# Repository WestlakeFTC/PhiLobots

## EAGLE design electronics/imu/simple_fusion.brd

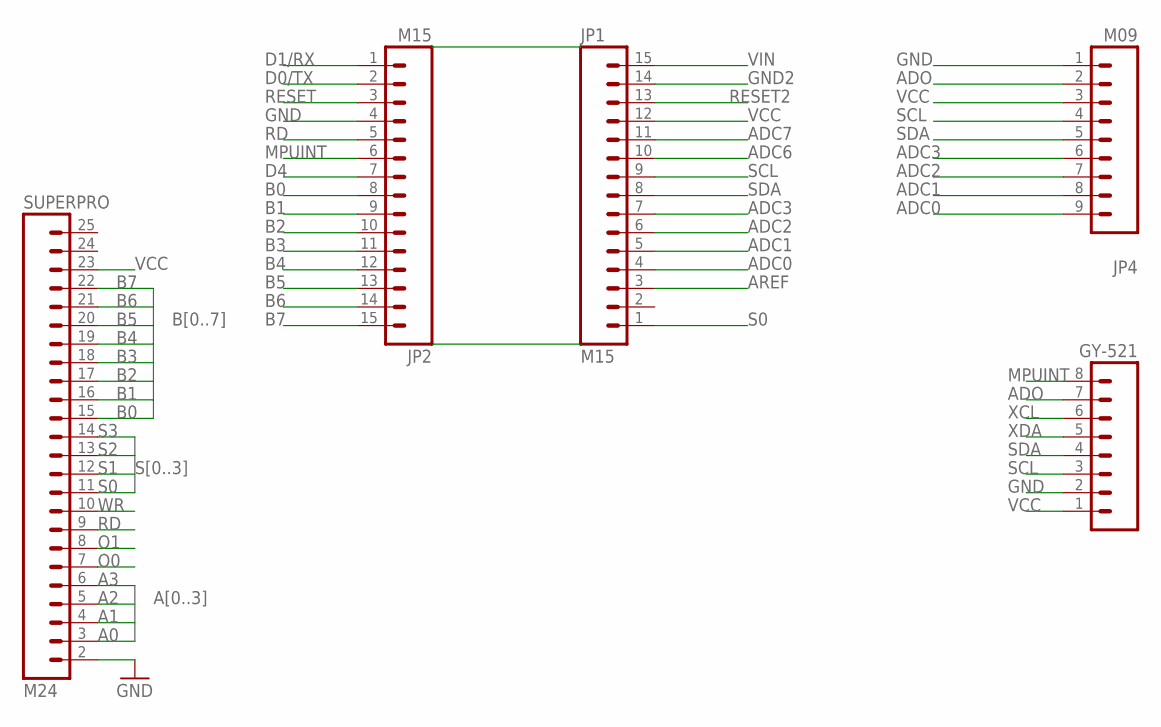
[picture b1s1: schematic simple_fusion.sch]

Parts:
GY-521: M081X08; 1X08
JP1, JP2: M15; 1X15
JP4: M09; 1X09
SUPERPRO: M24; 1X24

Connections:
A0: SUPERPRO.3
A1: SUPERPRO.4
A2: SUPERPRO.5
A3: SUPERPRO.6
ADC0: JP1.4, JP4.9
ADC1: JP1.5, JP4.8
ADC2: JP1.6, JP4.7
ADC3: JP1.7, JP4.6
ADC6: JP1.10
ADC7: JP1.11
ADO: GY-521.7, JP4.2
AREF: JP1.3
B0: JP2.8, SUPERPRO.15
B1: JP2.9, SUPERPRO.16
B2: JP2.10, SUPERPRO.17
B3: JP2.11, SUPERPRO.18
B4: JP2.12, SUPERPRO.19
B5: JP2.13, SUPERPRO.20
B6: JP2.14, SUPERPRO.21
B7: JP2.15, SUPERPRO.22
D0/TX: JP2.2
D1/RX: JP2.1
D4: JP2.7
GND: GY-521.2, JP2.4, JP4.1, SUPERPRO.2
GND2: JP1.14
MPUINT: GY-521.8, JP2.6
O0: SUPERPRO.7
O1: SUPERPRO.8
RD: JP2.5, SUPERPRO.9
RESET: JP2.3
RESET2: JP1.13
S0: JP1.1, SUPERPRO.11
S1: SUPERPRO.12
S2: SUPERPRO.13
S3: SUPERPRO.14
SCL: GY-521.3, JP1.9, JP4.4
SDA: GY-521.4, JP1.8, JP4.5
VCC: GY-521.1, JP1.12, JP4.3, SUPERPRO.23
VIN: JP1.15
WR: SUPERPRO.10
XCL: GY-521.6
XDA: GY-521.5

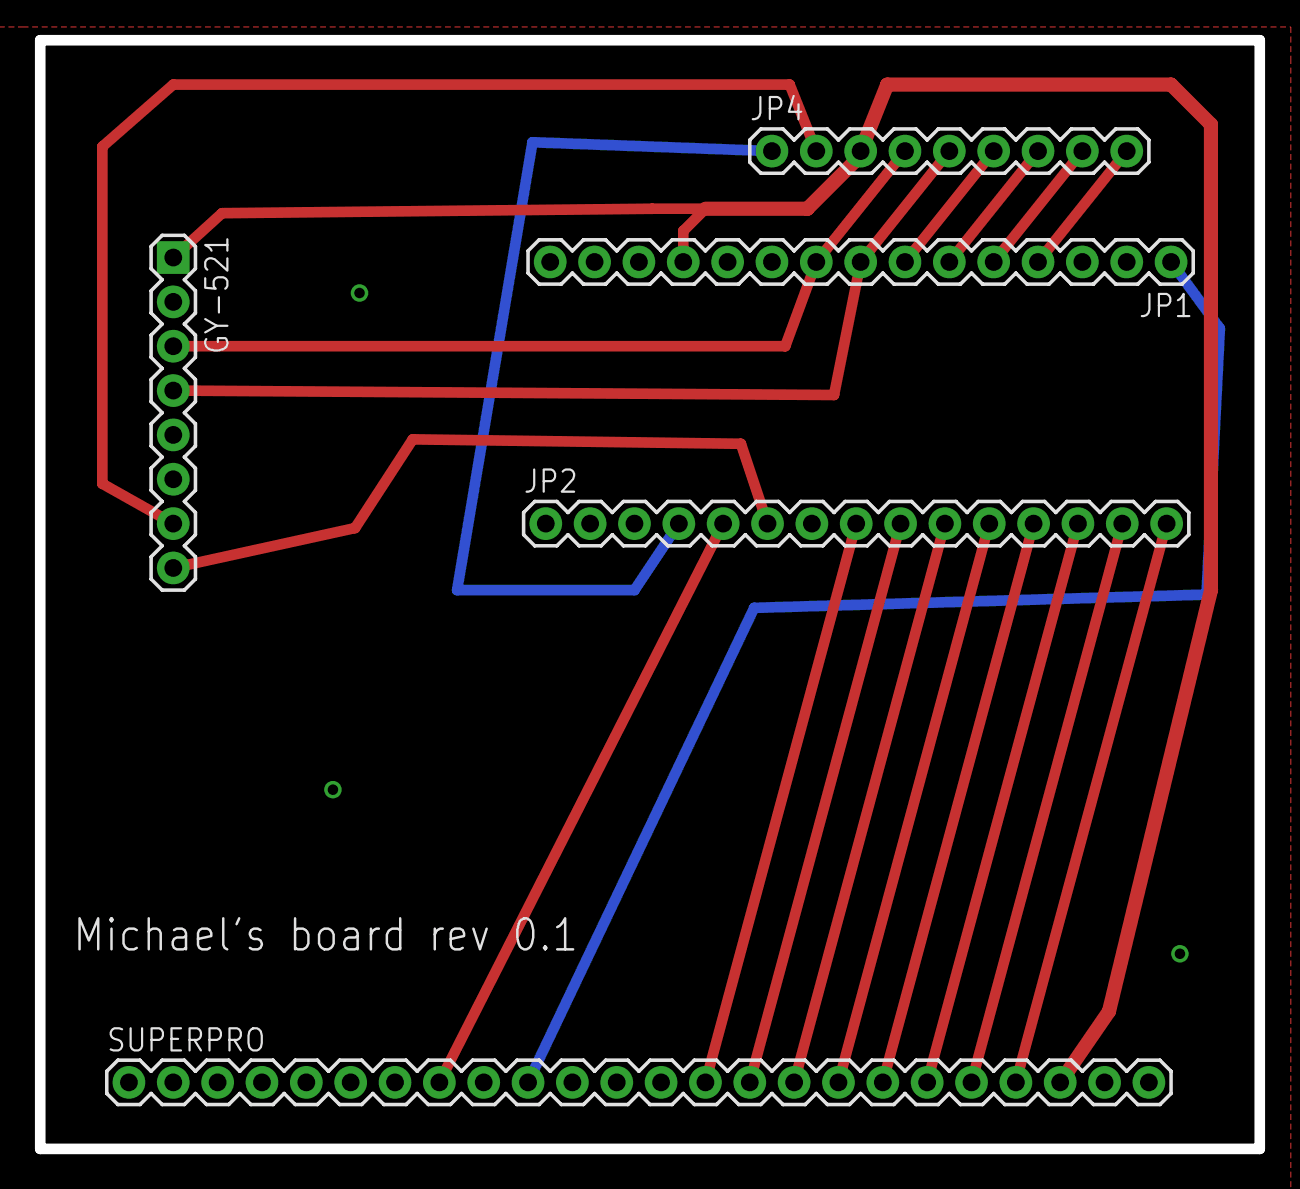
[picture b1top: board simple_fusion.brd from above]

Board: 2 copper layers, 69.8 x 63.5 mm, 5 parts (0 on the bottom side), 20 nets.

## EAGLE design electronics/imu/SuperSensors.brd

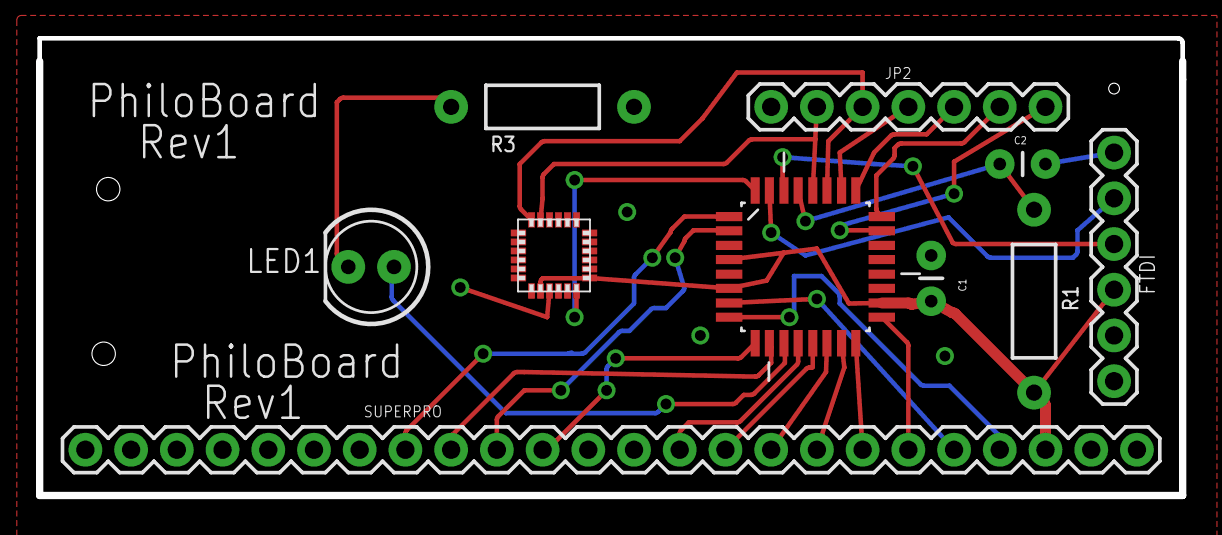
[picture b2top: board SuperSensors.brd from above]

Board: 2 copper layers, 63.5 x 25.3 mm, 10 parts (0 on the bottom side), 27 nets.

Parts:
C1, C2: 0.1uF; CAP-PTH-SMALL
FTDI: FTDI; 1X06
JP2: 1X07
LED1: 0.25W; LED5MM
R1, R3: 21K; AXIAL-0.4
SUPERPRO: M24; 1X24
U1: QFP80P900X900X120-32N
U$1: MPU-6050; QFN.24.4X4

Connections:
ADC0: JP2.7, U1.23
ADC1: JP2.6, U1.24
ADC2: JP2.5, U1.25
ADC3: JP2.4, U1.26
B0: SUPERPRO.15, U1.12
B1: SUPERPRO.16, U1.13
B2: SUPERPRO.17, U1.14
B3: SUPERPRO.18, U1.15
B4: SUPERPRO.19, U1.16
B5: SUPERPRO.20, U1.17
B6: SUPERPRO.21, U1.7
B7: SUPERPRO.22, U1.8
DTR: C2.1, FTDI.1
GND: C1.1, FTDI.6, JP2.1, R3.P$1, SUPERPRO.2, U1.3, U1.5, U1.21, U$1.9, U$1.18
MPUINT: U1.32, U$1.12
unnamed: LED1.A, U1.11
unnamed: LED1.K, R3.P$2
RD: SUPERPRO.9, U1.1
RESET: C2.2, R1.P$2, U1.29
RX: FTDI.3, U1.30
S0: SUPERPRO.11, U1.2
S1: SUPERPRO.12, U1.9
SCL: JP2.2, U1.28, U$1.23
SDA: JP2.3, U1.27, U$1.24
TX: FTDI.2, U1.31
VCC: C1.2, FTDI.4, R1.P$1, SUPERPRO.23, U1.4, U1.6, U1.18, U$1.8, U$1.13
WR: SUPERPRO.10, U1.10

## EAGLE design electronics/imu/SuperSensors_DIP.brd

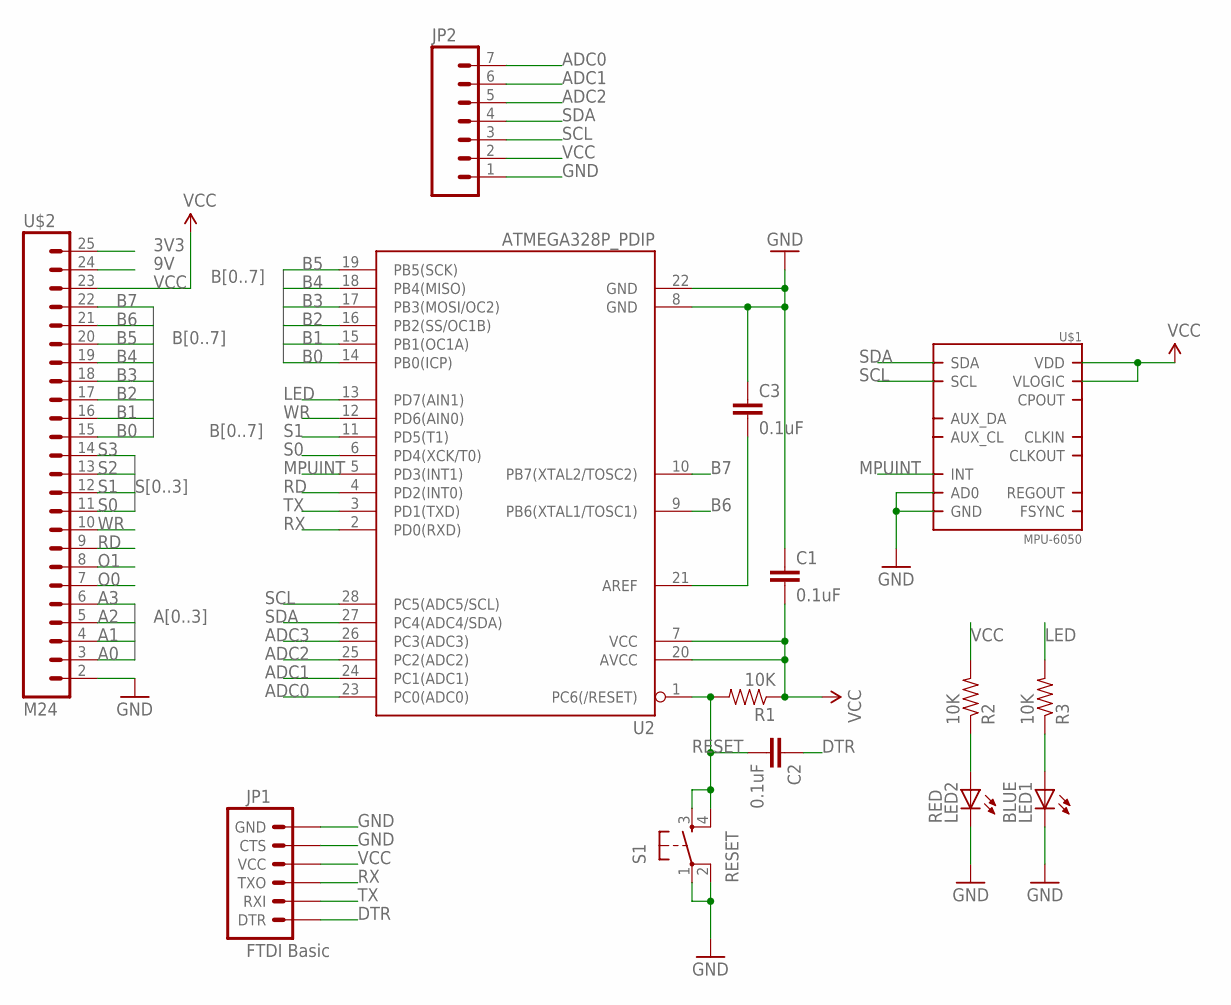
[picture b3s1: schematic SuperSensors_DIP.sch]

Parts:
C1, C2, C3: 0.1uF; CAP-PTH-SMALL
JP1: FTDI Basic; 1X06
JP2: M07; 1X07
LED1: BLUE; LED5MM
LED2: RED; LED5MM
R1, R2, R3: 10K; AXIAL-0.4
S1: RESET; TACTILE_SWITCH_SMD
U2: ATMEGA328P_PDIP; DIL28-3
U$1: MPU-6050; QFN.24.4X4
U$2: M24; 1X24

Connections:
3V3: U$2.25
9V: U$2.24
A0: U$2.3
A1: U$2.4
A2: U$2.5
A3: U$2.6
ADC0: JP2.7, U2.23 (PC0(ADC0))
ADC1: JP2.6, U2.24 (PC1(ADC1))
ADC2: JP2.5, U2.25 (PC2(ADC2))
ADC3: U2.26 (PC3(ADC3))
B0: U2.14 (PB0(ICP)), U$2.15
B1: U2.15 (PB1(OC1A)), U$2.16
B2: U2.16 (PB2(SS/OC1B)), U$2.17
B3: U2.17 (PB3(MOSI/OC2)), U$2.18
B4: U2.18 (PB4(MISO)), U$2.19
B5: U2.19 (PB5(SCK)), U$2.20
B6: U2.9 (PB6(XTAL1/TOSC1)), U$2.21
B7: U2.10 (PB7(XTAL2/TOSC2)), U$2.22
DTR: C2.1, JP1.1 (DTR)
GND: C1.1, C3.1, JP1.5 (CTS), JP1.6 (GND), JP2.1, LED1.K (C), LED2.K (C), S1.1, S1.2, U2.8 (GND), U2.22 (GND), U$1.9 (AD0), U$1.18 (GND), U$2.2
LED: R3.P$2 (2), U2.13 (PD7(AIN1))
MPUINT: U2.5 (PD3(INT1)), U$1.12 (INT)
unnamed: LED2.A, R2.P$1 (1)
unnamed: C3.2, U2.21 (AREF)
unnamed: LED1.A, R3.P$1 (1)
O0: U$2.7
O1: U$2.8
RD: U2.4 (PD2(INT0)), U$2.9
RESET: C2.2, R1.P$2 (2), S1.3, S1.4, U2.1 (PC6(/RESET))
RX: JP1.3 (TXO), U2.2 (PD0(RXD))
S0: U2.6 (PD4(XCK/T0)), U$2.11
S1: U2.11 (PD5(T1)), U$2.12
S2: U$2.13
S3: U$2.14
SCL: JP2.3, U2.28 (PC5(ADC5/SCL)), U$1.23 (SCL)
SDA: JP2.4, U2.27 (PC4(ADC4/SDA)), U$1.24 (SDA)
TX: JP1.2 (RXI), U2.3 (PD1(TXD))
VCC: C1.2, JP1.4 (VCC), JP2.2, R1.P$1 (1), R2.P$2 (2), U2.7 (VCC), U2.20 (AVCC), U$1.8 (VLOGIC), U$1.13 (VDD), U$2.23
WR: U2.12 (PD6(AIN0)), U$2.10

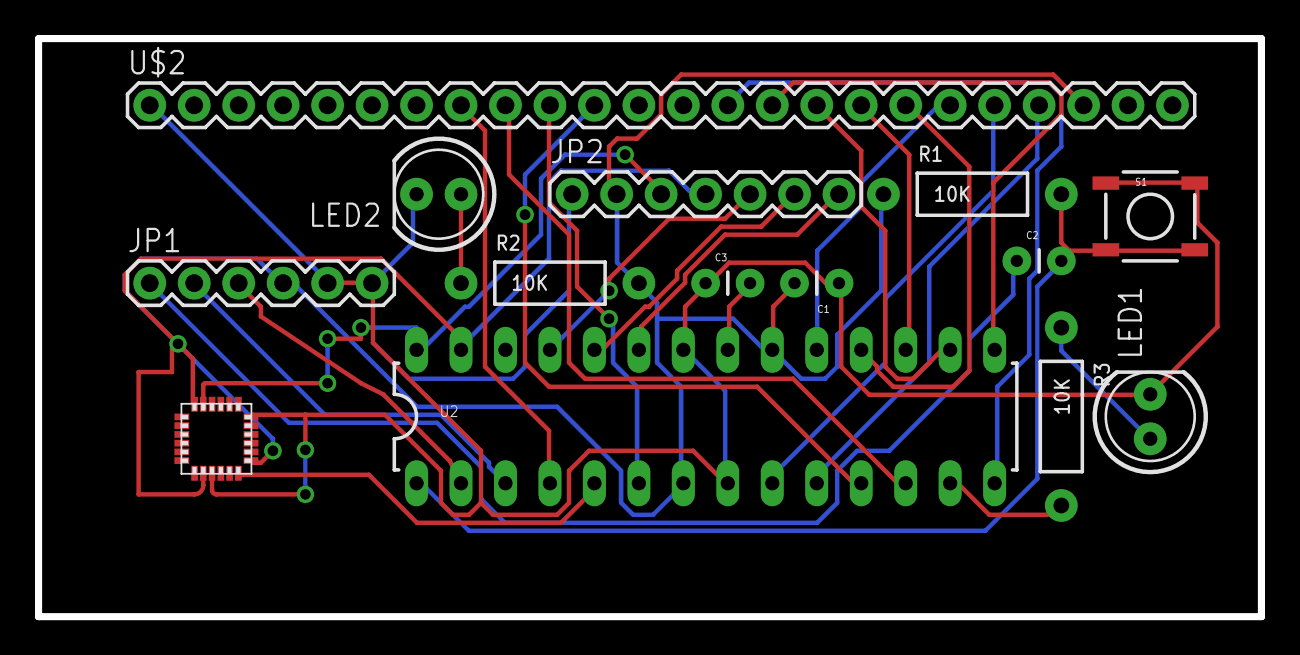
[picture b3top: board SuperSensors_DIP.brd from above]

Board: 2 copper layers, 69.8 x 33.0 mm, 14 parts (0 on the bottom side), 28 nets.

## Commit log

2014-10-23 add current prototype
2014-10-31 more prototyping
    added encoder, sonar sensor code
    clean up too
    added draft autonomous
2014-11-05 Autonomous TroubleShoot
    fixed turn function
2014-11-19 added predicted and observed offset
2014-11-24 teleop
    updated systems
2014-11-26 teleop for insertion
    first version
2014-11-28 Button woes resolved
    figured out unresponsive button problem with debouncing
2014-11-28 faucet direction
    aiming system
2014-11-29 Using objects in robotC? Mind Explosion
    Definition of object like structure to debounce every button
2014-11-29 name consistency + glass jar resolution
2014-11-29 control
2014-11-29 Autonomous + glass jar resolution
2014-11-29 same code except for one 1
2014-12-02 Lift control
    add lift control, also clean up a little
2014-12-02 adjust lift control
    make it less sensitive so more accurate control
2014-12-03 parkinglot autonomous
    fine tuned the movements
2014-12-03 grabber control
    add grabber control with d-pad (top hat) buttons
2014-12-05 Ramp+teleop
2014-12-05 clean up ultrasound
    assume position 3 when in doubt
2014-12-05 comments
    add/adjust comments
2014-12-06 reconfigure
    reconfigure to match current eclectronics
    adjust trailer
    add ramp to goal autonomous
2014-12-06 practice
    adjust based on practice
2014-12-06 ramp
    match ramp numbers to parking lot testing
2014-12-06 adjust
    ramp2goal
2014-12-25 shinning new grabber
    and some attempt on ramp autonomous strategy
2015-01-01 grabber work for most cases
    still need work on cases when goal is at horizontal
2015-01-01 working grabber backup
    The grabber work for pretty much everything but imma make it better
2015-01-01 Working grabber back up is the best option
2015-01-08 initial schematics for sensor board
2015-01-09 adjust wiggle to goal
    slowed down some speeds and added slower turn to wiggle
2015-01-11 lots of changes
    Multiplexer is here too
2015-01-11 flapper installed
    initial positions for flappers for teleop
2015-01-16 gear ratio
2015-01-17 board layout
2015-01-17 fixing some short circuits
2015-01-23 tune for new driver train
2015-01-23 more tune
2015-01-24 add comments
2015-01-30 cleanup and reconfig
    getting ready for connally tour
2015-02-06 more formatting and cleaning
2015-02-06 chnge gear ratio and work on ramp
2015-02-06 created simple board
    combine GY-521, superpro, arduino
    nano using a bare minimum PCB
2015-02-06 check in cleaned up code for comps
2015-02-06 smux code
2015-02-07 temp check in
2015-02-07 Ramp and Sonar
    Added sonar sensor to the side of robot to align with wall
2015-02-10 modify competition code
    add mux sensors
    center goal logic
    and tests
2015-02-11 added servo flappers
    servo flapper3 powers intake
    added reverse flappers function
2015-02-11 move teleop
    more cleanup
    add more accurate motor sync
2015-02-13 TeleOp changes
    reversed min and max values for lift
    lift now works well during Teleop
    added btn and methods for hingeFaucet
2015-02-14 new changes to faucet
    added spout servo as trap door
    modified hingeFaucet
    added intake control to fansOn
    modified distances in Ramp
2015-02-17 add superpro board
2015-02-18 adjustments to ramp and drive
2015-02-18 filter bogus encoders
2015-02-20 reconfig teleop
2015-02-20 arduino side code
2015-02-20 fine tune mpu based controllers
    made scanGoal work
2015-02-21 initilization for auto initialization on ramp
2015-02-21 clean up a little
2015-02-21 plan for ramp
2015-02-21 warning on superpro failure
    reset power
2015-02-23 change for comp
2015-02-27 filter out erroneous encoder values
2015-03-02 found a bug in gyro driver
2015-03-02 added mpu turn and move with odometer
2015-03-04 tuning for MPU straight move and turns
2015-03-09 tuning parking lot and ramp
    reconfigured to move MidR motor to flapper
    scanning goal functions mostly working
    ramp can score two goals
2015-03-09 one file missed
2015-03-10 tuned scanning
    cleaned up westcoaster
    make more moves in parking lot
    fixed scanning for inconsistent sonar readings
2015-03-19 competition code at super regional
    code from Manuj email
2015-03-25 tuning
    Found a loose screw which is caught in drive train at random times,
    causing one side of wheels not moving. That is probably cause for the
    wrong turn on the ramp during competition.
    After removing the screw, robot behaves much more consistent.
    Tuned ramp autonomous. Most of time we can get two goals parking lot.
    Lift, dropping balls are not yet tested.
2015-03-27 factor out angleTurned
2015-03-27 Clean up code not used
    remove pitch and roll from interface
    remove dead code in super sensors
2015-03-27 relax latency requirement for superpro
2015-03-27 change tests for compiling
2015-03-27 works very well
    added a small correction at bottom of ramp
2015-04-01 change for lift
2015-04-01 add a semi
2015-04-02 tested lift on motor
2015-04-03 roller w/ 2 servos
2015-04-04 LIFT with motor test 1
    note that some slop in lift and lift does not go all the way the down so
    values are therefore a little off
2015-04-05 tuned for the ramp
2015-04-05 check in some logs for analysis later
2015-04-05 some cleanup
    also fix a bug for angle calculation when crossing from negative to
    positive at 180 bound
2015-04-10 tuning
2015-04-11 fine tuning
2015-04-11 turn on waitforstart and check for lift
2015-04-11 testing
    Conflicts:
    competition/Ramp.c
2015-04-11 do not use bad encoders
2015-04-12 improved filtering
2015-04-12 guard against superpro init
2015-04-13 add sonar to super sensors
2015-04-13 comparison tests
2015-04-13 center goal detection
2015-04-14 tentative center goal
2015-04-14 add timeout for oneshot
2015-04-14 cleanup blocking and nonblocking calls
2015-04-14 switch between MPU and encoders
2015-04-15 delay
2015-04-15 tune
2015-04-15 turnoff ramping after ramp down
2015-04-18 final ramp for competition
2015-04-18 changes in defs
2015-04-19 tested final version for parking
2015-04-19 add waitForStart
2015-04-24 ramping up fan and safe parking
2015-04-24 defensive parking
2015-04-24 remove center goal code from ramp
2015-04-25 competition today
2015-04-25 whitepaper
2015-04-25 ramping fan for auto

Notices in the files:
parts and their libraries:
SparkFun-Capacitors: Licensing: CC v3.0 Share-Alike You are welcome to use this library for commercial purposes.
